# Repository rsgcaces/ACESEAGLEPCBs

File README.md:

# ACESEAGLEPCBs
Email Mr. D. if there is a design in the [ACES PCB Archive](http://darcy.rsgc.on.ca/ACES/PCBs/index.html) that you would like access to and he'll add it.

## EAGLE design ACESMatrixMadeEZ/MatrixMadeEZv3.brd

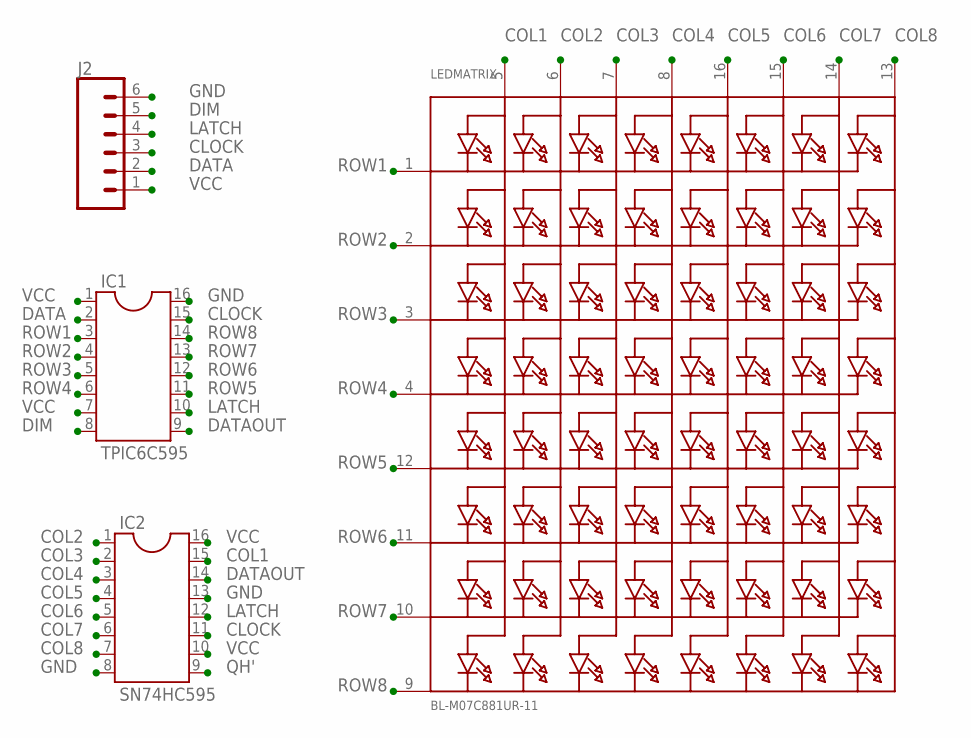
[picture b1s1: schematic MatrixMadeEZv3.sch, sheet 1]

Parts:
IC1: TPIC6C595; DIL16
IC2: SN74HC595; DIL16
J2: CONN_06LONGPADS; 1X06_LONGPADS
LEDMATRIX: BL-M07C881UR-11; SEGMENT_BL-M07C881UR

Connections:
CLOCK: IC1.15, IC2.11, J2.3
COL1: IC2.15, LEDMATRIX.5 (A1)
COL2: IC2.1, LEDMATRIX.6 (A2)
COL3: IC2.2, LEDMATRIX.7 (A3)
COL4: IC2.3, LEDMATRIX.8 (A4)
COL5: IC2.4, LEDMATRIX.16 (A5)
COL6: IC2.5, LEDMATRIX.15 (A6)
COL7: IC2.6, LEDMATRIX.14 (A7)
COL8: IC2.7, LEDMATRIX.13 (A8)
DATA: IC1.2, J2.2
DATAOUT: IC1.9, IC2.14
DIM: IC1.8, J2.5
GND: IC1.16, IC2.8, IC2.13, J2.6
LATCH: IC1.10, IC2.12, J2.4
QH': IC2.9
ROW1: IC1.3, LEDMATRIX.1 (K1)
ROW2: IC1.4, LEDMATRIX.2 (K2)
ROW3: IC1.5, LEDMATRIX.3 (K3)
ROW4: IC1.6, LEDMATRIX.4 (K4)
ROW5: IC1.11, LEDMATRIX.12 (K5)
ROW6: IC1.12, LEDMATRIX.11 (K6)
ROW7: IC1.13, LEDMATRIX.10 (K7)
ROW8: IC1.14, LEDMATRIX.9 (K8)
VCC: IC1.1, IC1.7, IC2.10, IC2.16, J2.1

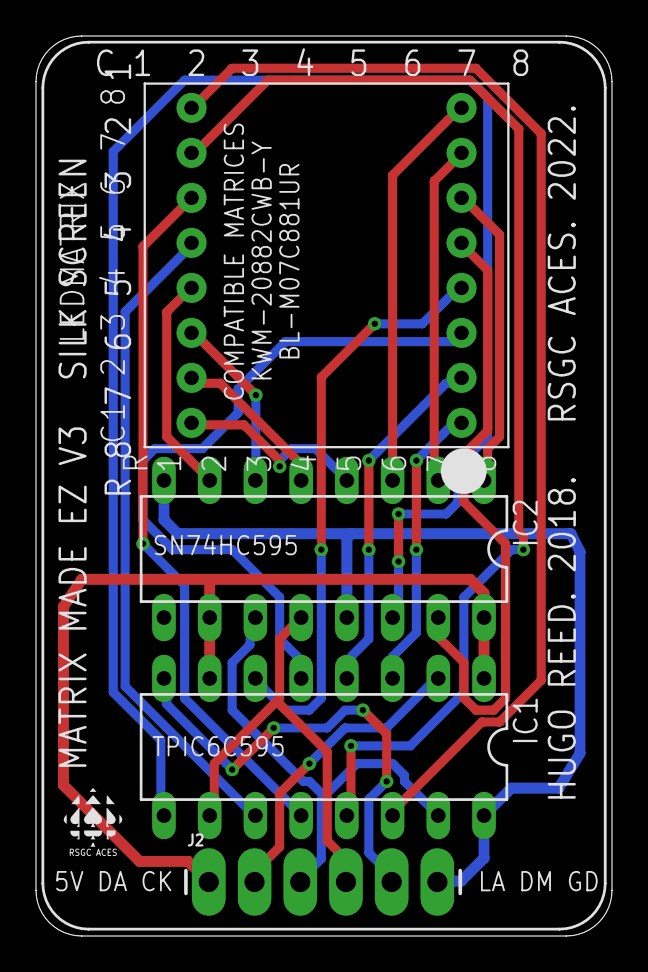
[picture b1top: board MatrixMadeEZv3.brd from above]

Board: 2 copper layers, 32.0 x 50.0 mm, 6 parts (0 on the bottom side), 23 nets.

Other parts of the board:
U$1: SMALL_TSILK_TEXT
U$6: SMALL_BSILK_TEXT

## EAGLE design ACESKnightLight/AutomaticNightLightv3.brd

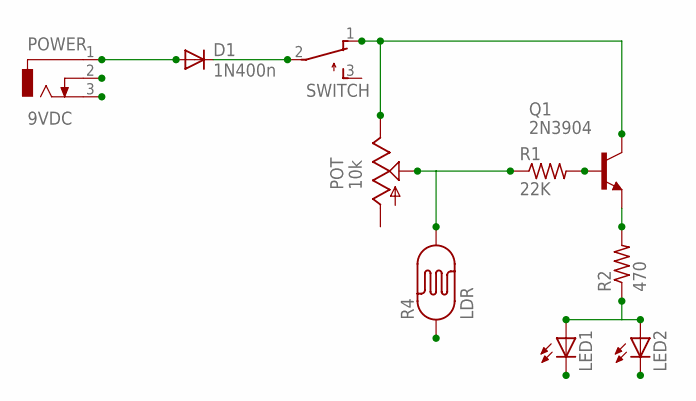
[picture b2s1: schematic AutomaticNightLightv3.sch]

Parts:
D1: 1N400n; DO41-10
LED1, LED2: LED5MM
POT: 10k; S64W
POWER: 9VDC; PJ-202AH
Q1: 2N3904; TO92-EBC-OVAL
R1: 22K; 0207/10
R2: 470; 0207/10
R4: LDR; PHOTOCELL
SWITCH: TL32PO; TL3XPO

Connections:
GND: LED1.K (C), LED2.K (C), POWER.2, POWER.3, R4.1
unnamed: D1.A, POWER.1
unnamed: D1.C, SWITCH.2
unnamed: Q1.B, R1.2
unnamed: Q1.E, R2.2
unnamed: POT.S, R1.1, R4.2
unnamed: POT.E, Q1.C, SWITCH.1 (O)
unnamed: LED1.A, LED2.A, R2.1

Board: 2 copper layers, 11 parts (0 on the bottom side), 8 nets, no tracks yet.

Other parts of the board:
U$1: MEDIUM_TSILK_TEXT

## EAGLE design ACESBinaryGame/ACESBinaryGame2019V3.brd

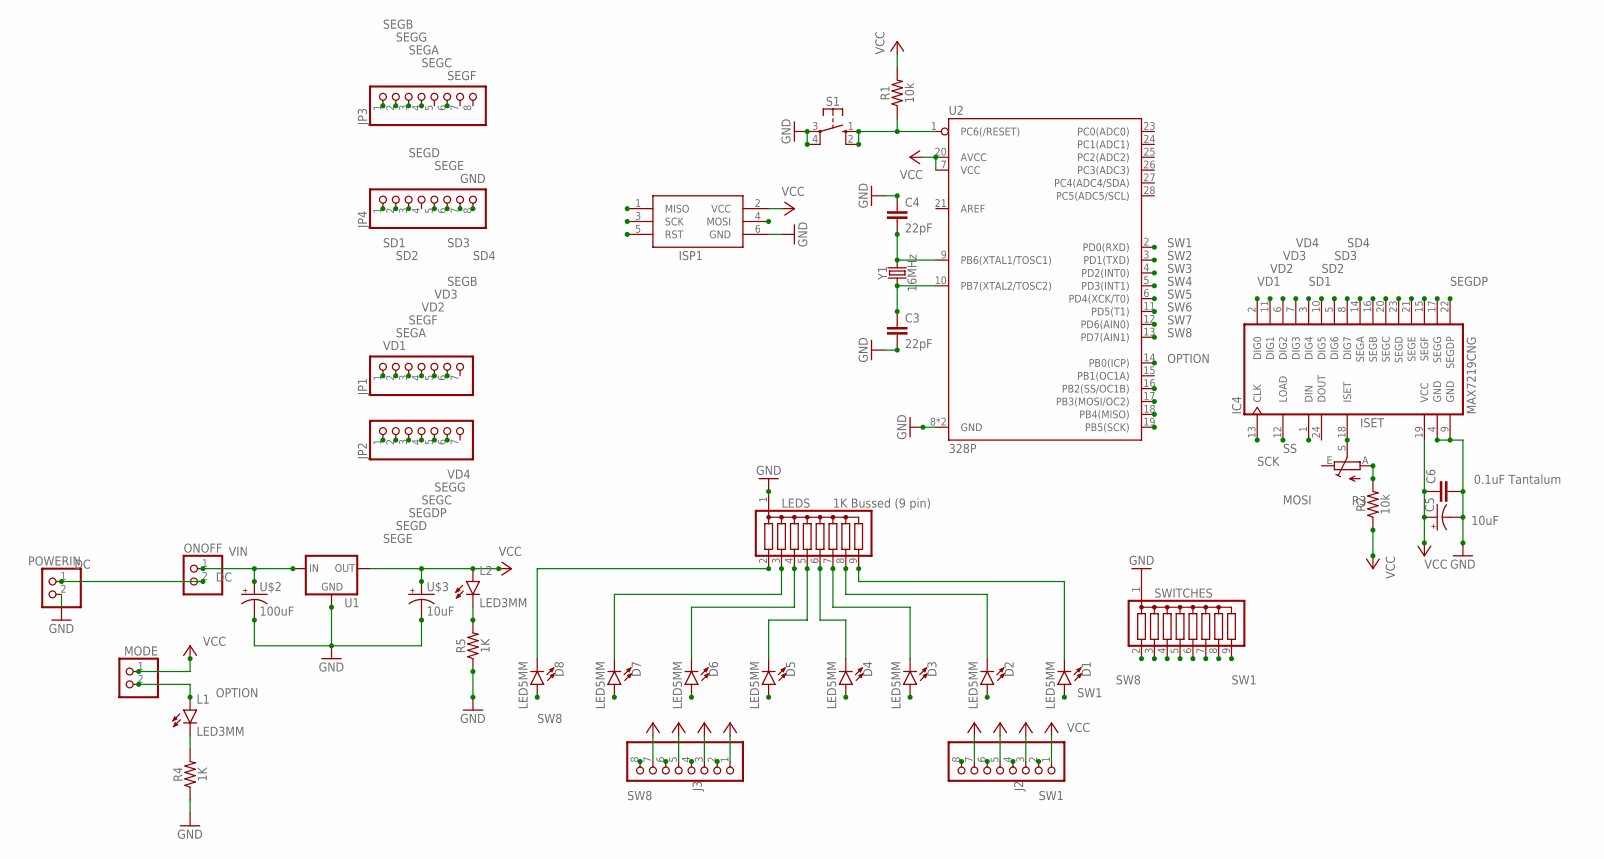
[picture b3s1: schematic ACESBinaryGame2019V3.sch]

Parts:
C3, C4: 22pF; CAP-PTH-2.54
C5: 10uF; CPOL-RADIAL-2.5MM-5MM
C6: 0.1uF Tantalum; CAP-PTH-2.54
D1, D2, D3, D4, D5, D6, D7, D8: LED5MM
IC4: MAX7219CNG; DIL24-3
ISP1: AVRISP-6; AVRISP
J2, J3: PINHD-1X8-3.5MM; 1X08-3.5MM
JP1, JP2: PINHD-1X7; 1X07
JP3, JP4: PINHD-1X8; 1X08
L1, L2: LED3MM
LEDS: 1K Bussed (9 pin); SIL9
MODE: PINHD-1X2; 1X02
ONOFF: PINHD-1X2; 1X02
POWERIN: PINHD-1X2; 1X02
R1, R2: 10k; AXIAL-0.3
R3: TRIM_EU-B25P; B25P
R4, R5: 1K; AXIAL-0.3
S1: MOMENTARY_BUTTONS; B3F-40XX
SWITCHES: G08R; SIL9
U1: LM78XX; 78XXL
U2: 328P; DIP28
U$2: 100uF; CPOL-RADIAL-2.5MM-5MM
U$3: 10uF; CPOL-RADIAL-2.5MM-5MM
Y1: 16MHz; HC49US

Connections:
DC: ONOFF.2, POWERIN.1
GND: C3.2, C4.1, C5.2 (-), C6.2, IC4.4 (GND), IC4.9 (GND), ISP1.6 (GND), JP4.7, LEDS.1, POWERIN.2, R4.P$1 (1), R5.P$1 (1), S1.3, S1.4 (P1), SWITCHES.1, U1.GND, U2.8 (GND), U2.22 (GND), U$2.2 (-), U$3.2 (-)
ISET: IC4.18 (ISET), R3.S
MISO: ISP1.1 (MISO), U2.18 (PB4(MISO))
MOSI: IC4.1 (DIN), ISP1.4 (MOSI), U2.17 (PB3(MOSI/OC2))
unnamed: L1.K (C), R4.P$2 (2)
unnamed: C3.1, U2.10 (PB7(XTAL2/TOSC2)), Y1.1
unnamed: C4.2, U2.9 (PB6(XTAL1/TOSC1)), Y1.2
unnamed: R2.P$2 (2), R3.A
unnamed: L2.K (C), R5.P$2 (2)
unnamed: D1.K (C), LEDS.9
unnamed: D2.K (C), LEDS.8
unnamed: D3.K (C), LEDS.7
unnamed: D4.K (C), LEDS.6
unnamed: D5.K (C), LEDS.5
unnamed: D6.K (C), LEDS.4
unnamed: D7.K (C), LEDS.3
unnamed: D8.K (C), LEDS.2
OPTION: L1.A, MODE.2, U2.14 (PB0(ICP))
RST: ISP1.5 (RST), R1.P$1 (1), S1.1 (S), S1.2 (S1), U2.1 (PC6(/RESET))
SCK: IC4.13 (CLK), ISP1.3 (SCK), U2.19 (PB5(SCK))
SD1: IC4.3 (DIG4), JP4.1
SD2: IC4.10 (DIG5), JP4.2
SD3: IC4.5 (DIG6), JP4.6
SD4: IC4.8 (DIG7), JP4.8
SEGA: IC4.14 (SEGA), JP1.2, JP3.3
SEGB: IC4.16 (SEGB), JP1.6, JP3.1
SEGC: IC4.20 (SEGC), JP2.4, JP3.4
SEGD: IC4.23 (SEGD), JP2.2, JP4.3
SEGDP: IC4.22 (SEGDP), JP2.3
SEGE: IC4.21 (SEGE), JP2.1, JP4.5
SEGF: IC4.15 (SEGF), JP1.3, JP3.6
SEGG: IC4.17 (SEGG), JP2.5, JP3.2
SS: IC4.12 (LOAD), U2.16 (PB2(SS/OC1B))
SW1: D1.A, J2.2, SWITCHES.9, U2.2 (PD0(RXD))
SW2: D2.A, J2.4, SWITCHES.8, U2.3 (PD1(TXD))
SW3: D3.A, J2.6, SWITCHES.7, U2.4 (PD2(INT0))
SW4: D4.A, J2.8, SWITCHES.6, U2.5 (PD3(INT1))
SW5: D5.A, J3.2, SWITCHES.5, U2.6 (PD4(XCK/T0))
SW6: D6.A, J3.4, SWITCHES.4, U2.11 (PD5(T1))
SW7: D7.A, J3.6, SWITCHES.3, U2.12 (PD6(AIN0))
SW8: D8.A, J3.8, SWITCHES.2, U2.13 (PD7(AIN1))
VCC: C5.1 (+), C6.1, IC4.19 (VCC), ISP1.2 (VCC), J2.1, J2.3, J2.5, J2.7, J3.1, J3.3, J3.5, J3.7, L2.A, MODE.1, R1.P$2 (2), R2.P$1 (1), U1.OUT, U2.7 (VCC), U2.20 (AVCC), U$3.1 (+)
VD1: IC4.2 (DIG0), JP1.1
VD2: IC4.11 (DIG1), JP1.4
VD3: IC4.6 (DIG2), JP1.5
VD4: IC4.7 (DIG3), JP2.6
VIN: ONOFF.1, U1.IN, U$2.1 (+)

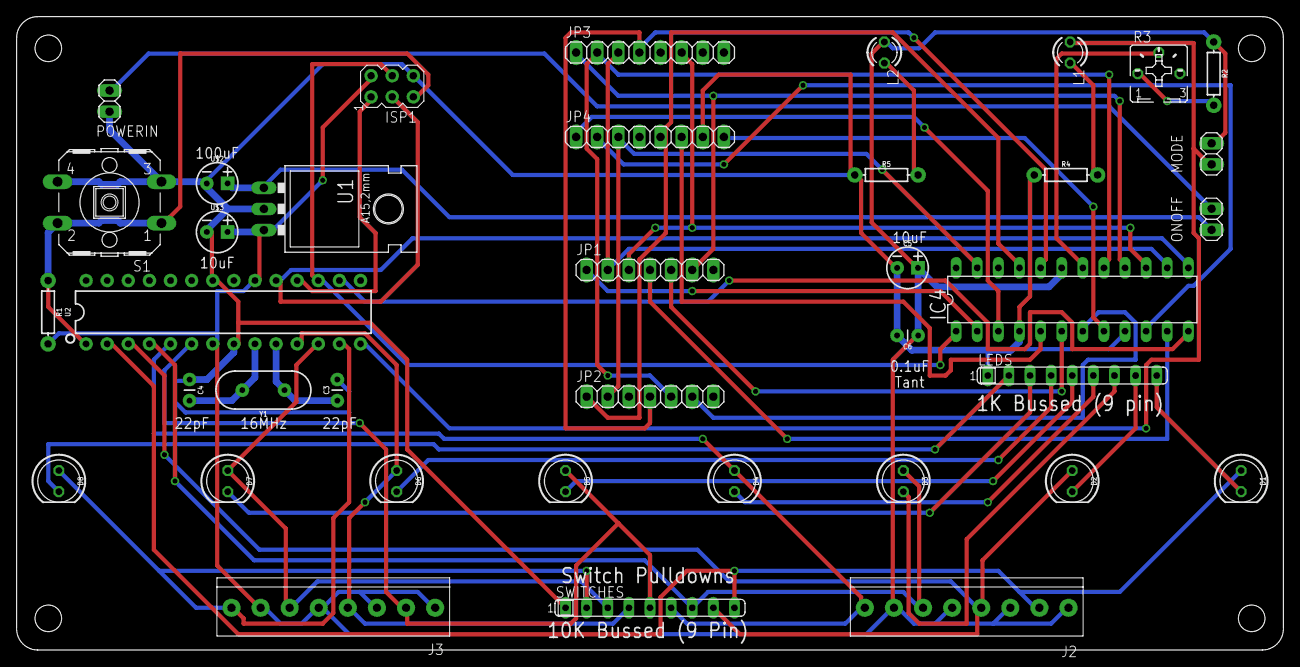
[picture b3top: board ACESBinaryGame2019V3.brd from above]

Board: 2 copper layers, 152.4 x 76.2 mm, 39 parts (0 on the bottom side), 48 nets.

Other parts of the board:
U$1: ACES_LOGO_MEDIUM

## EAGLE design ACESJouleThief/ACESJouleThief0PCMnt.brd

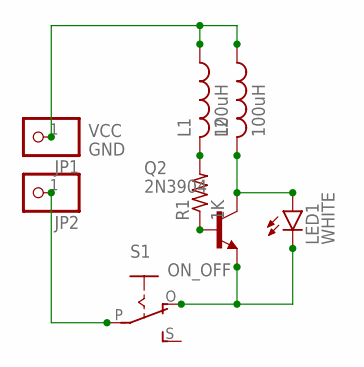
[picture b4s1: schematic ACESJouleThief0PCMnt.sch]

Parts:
JP1, JP2: PINHD-1X1; 1X01
L1, L2: 100uH; 0207/10
LED1: WHITE; LED_5MM
Q2: 2N3904; TO92-EBC
R1: 1K; 0207/10
S1: ON_OFF; EG1218

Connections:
GND: JP2.1, S1.P
unnamed: Q2.B, R1.1
unnamed: LED1.K (C), Q2.E, S1.O
unnamed: L2.2, LED1.A, Q2.C
unnamed: L1.2, R1.2
VCC: JP1.1, L1.1, L2.1

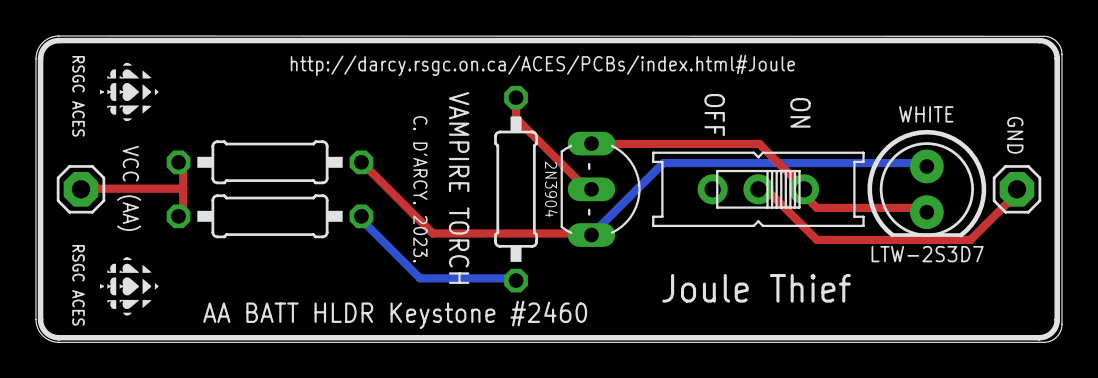
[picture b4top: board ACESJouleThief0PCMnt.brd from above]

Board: 2 copper layers, 57.0 x 17.0 mm, 11 parts (0 on the bottom side), 6 nets.

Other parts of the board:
U$1, U$2: SMALL_TSILK
U$3: MEDIUM_BSILK_TEXT

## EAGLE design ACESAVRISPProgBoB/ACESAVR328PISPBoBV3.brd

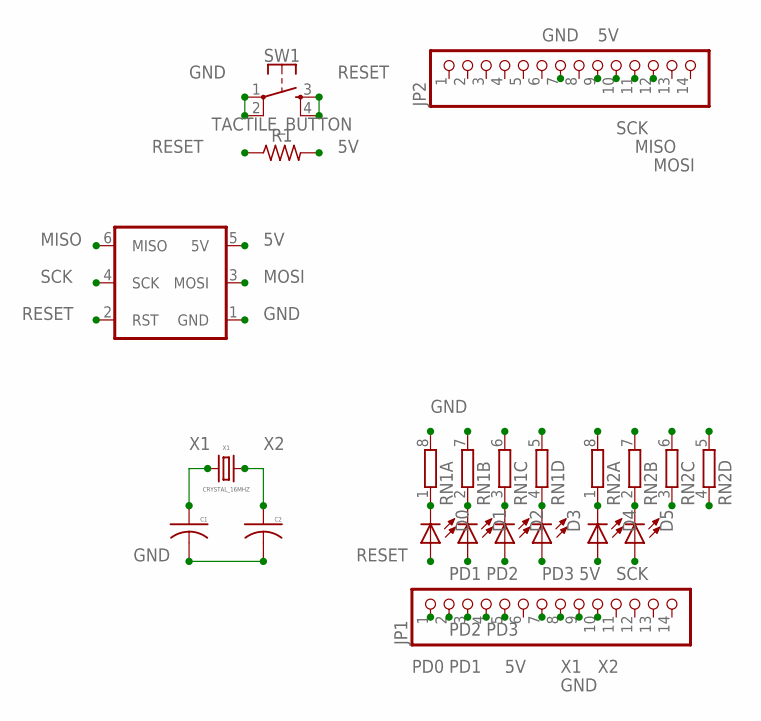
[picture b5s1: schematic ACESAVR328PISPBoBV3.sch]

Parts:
C1, C2: C-USC0603K; C0603K
D0, D1, D2, D3: BLUE; CHIP-LED0603
D4: RED; CHIP-LED0603
D5: GREEN; CHIP-LED0603
H1: ISP_HEADER; ICSP
JP1, JP2: PINHD-1X14; 1X14
R1: R-US_R0603; R0603
RN1, RN2: 4R-N0603-ARC; 0603-ARC
SW1: TACTILE_BUTTON; TACTILE_BUTTON_SMD_5.2MM
X1: CRYSTAL_16MHZ; HC49US

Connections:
5V: D4.A, H1.5 (5V), JP1.7, JP2.9, R1.2
GND: C1.2, C2.2, H1.1 (GND), JP1.8, JP2.7, RN1.5 (2), RN1.6 (2), RN1.7 (2), RN1.8 (2), RN2.5 (2), RN2.6 (2), RN2.7 (2), RN2.8 (2), SW1.1, SW1.2
MISO: H1.6 (MISO), JP2.11
MOSI: H1.3 (MOSI), JP2.12
unnamed: D0.C, RN1.1
unnamed: D1.C, RN1.2 (1)
unnamed: D2.C, RN1.3 (1)
unnamed: D3.C, RN1.4 (1)
unnamed: D4.C, RN2.1
unnamed: D5.C, RN2.2 (1)
PD0: D0.A, JP1.2
PD1: D1.A, JP1.3
PD2: D2.A, JP1.4
PD3: D3.A, JP1.5
RESET: H1.2 (RST), JP1.1, R1.1, SW1.3, SW1.4
SCK: D5.A, H1.4 (SCK), JP2.10
X1: C1.1, JP1.9, X1.1
X2: C2.1, JP1.10, X1.2

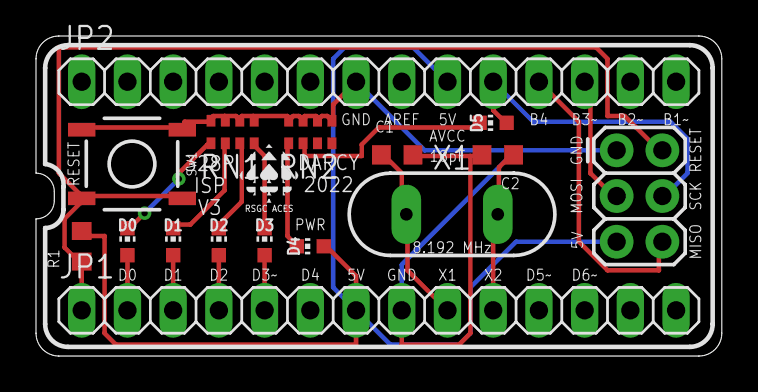
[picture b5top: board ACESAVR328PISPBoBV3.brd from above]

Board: 2 copper layers, 38.1 x 17.8 mm, 17 parts (0 on the bottom side), 18 nets.

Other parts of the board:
U$1: SMALL_TSILK_TEXT

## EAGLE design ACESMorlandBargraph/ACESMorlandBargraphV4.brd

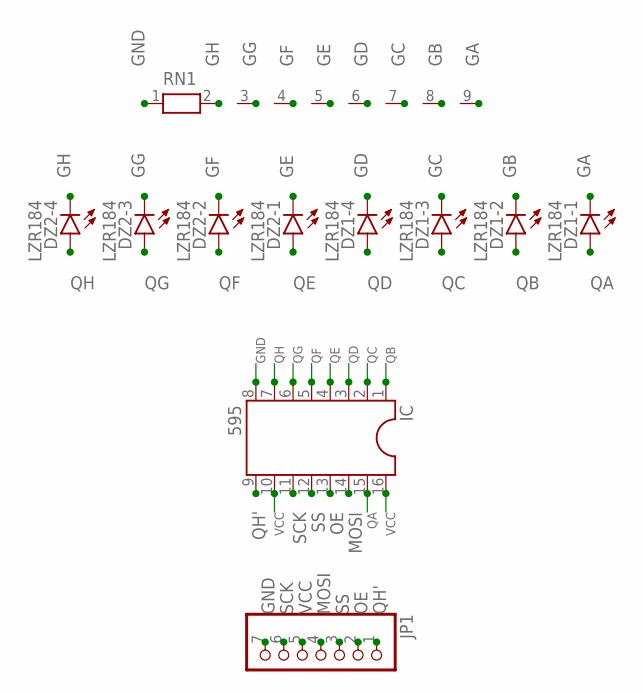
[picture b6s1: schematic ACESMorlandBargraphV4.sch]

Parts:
DZ1, DZ2: LZR184
IC: 595; DIL16
JP1: PINHD-1X7/90; 1X07/90
RN1: RN08; RN-9

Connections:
GA: DZ1.K1 (C), RN1.9
GB: DZ1.K2 (C), RN1.8
GC: DZ1.K3 (C), RN1.7
GD: DZ1.K4 (C), RN1.6
GE: DZ2.K1 (C), RN1.5
GF: DZ2.K2 (C), RN1.4
GG: DZ2.K3 (C), RN1.3
GH: DZ2.K4 (C), RN1.2
GND: IC.8, JP1.7, RN1.1
MOSI: IC.14, JP1.4
OE: IC.13, JP1.2
QA: DZ1.A1 (A), IC.15
QB: DZ1.A2 (A), IC.1
QC: DZ1.A3 (A), IC.2
QD: DZ1.A4 (A), IC.3
QE: DZ2.A1 (A), IC.4
QF: DZ2.A2 (A), IC.5
QG: DZ2.A3 (A), IC.6
QH: DZ2.A4 (A), IC.7
QH': IC.9, JP1.1
SCK: IC.11, JP1.6
SS: IC.12, JP1.3
VCC: IC.10, IC.16, JP1.5

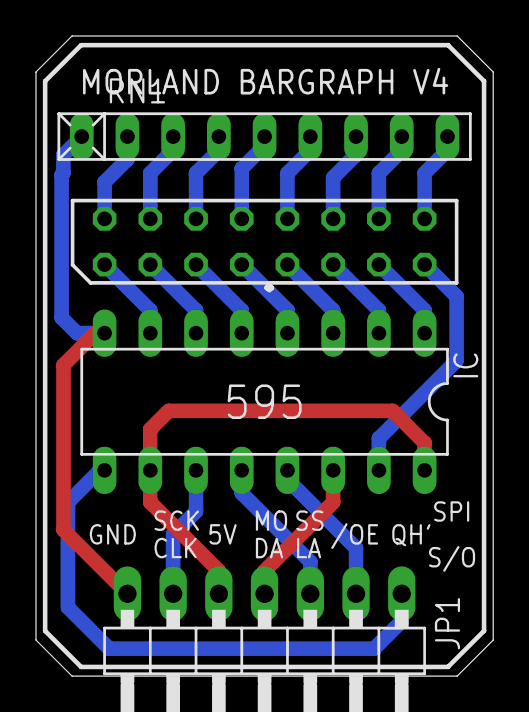
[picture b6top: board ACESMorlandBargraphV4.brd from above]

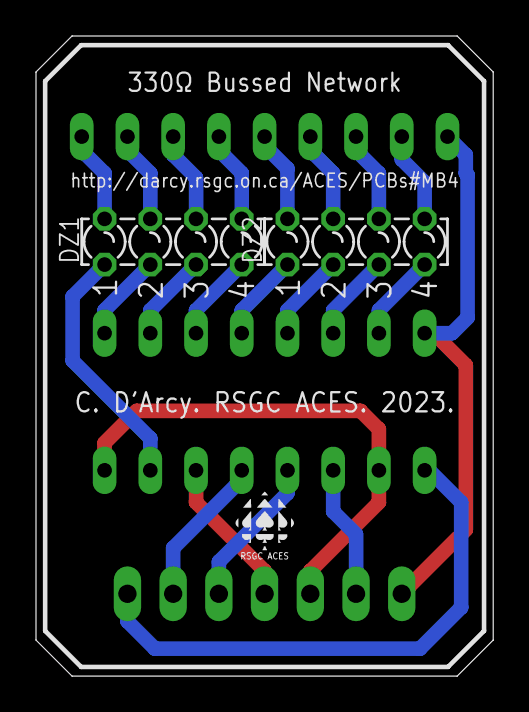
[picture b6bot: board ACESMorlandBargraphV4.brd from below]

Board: 2 copper layers, 25.4 x 35.6 mm, 6 parts (2 on the bottom side), 23 nets.

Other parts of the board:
U$1: SMALL_BSILK_TEXT

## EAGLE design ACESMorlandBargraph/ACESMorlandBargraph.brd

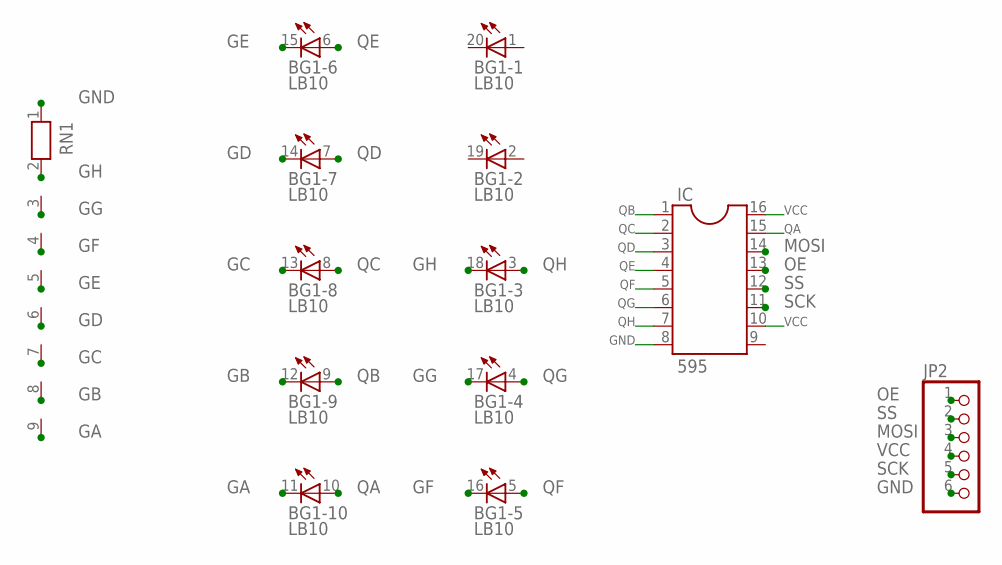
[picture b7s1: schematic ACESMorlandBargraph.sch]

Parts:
BG1: LB10
IC: 595; DIL16
JP2: PINHD-1X6/90; 1X06/90
RN1: RN08; RN-9

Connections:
GA: BG1.11 (C), RN1.9
GB: BG1.12 (C), RN1.8
GC: BG1.13 (C), RN1.7
GD: BG1.14 (C), RN1.6
GE: BG1.15 (C), RN1.5
GF: BG1.16 (C), RN1.4
GG: BG1.17 (C), RN1.3
GH: BG1.18 (C), RN1.2
GND: IC.8, JP2.6, RN1.1
MOSI: IC.14, JP2.3
OE: IC.13, JP2.1
QA: BG1.10 (A), IC.15
QB: BG1.9 (A), IC.1
QC: BG1.8 (A), IC.2
QD: BG1.7 (A), IC.3
QE: BG1.6 (A), IC.4
QF: BG1.5 (A), IC.5
QG: BG1.4 (A), IC.6
QH: BG1.3 (A), IC.7
SCK: IC.11, JP2.5
SS: IC.12, JP2.2
VCC: IC.10, IC.16, JP2.4

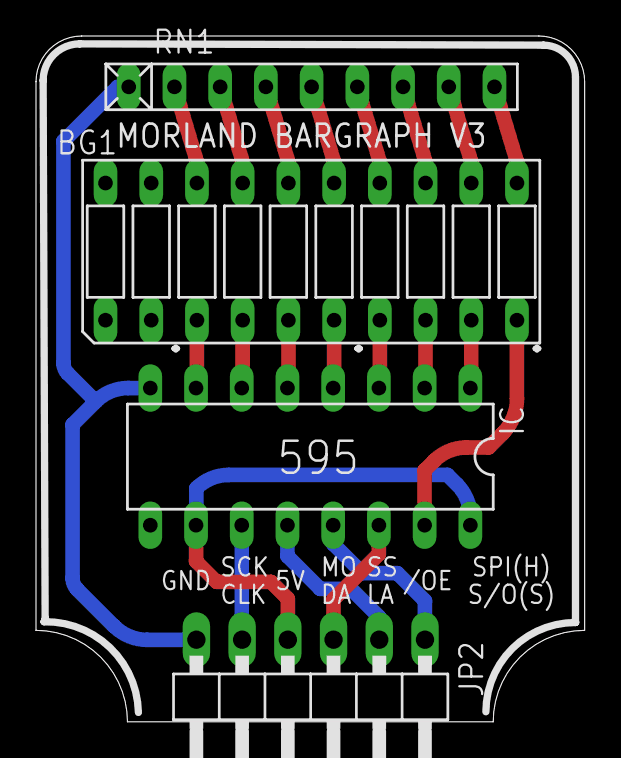
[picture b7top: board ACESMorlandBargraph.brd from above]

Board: 2 copper layers, 30.5 x 38.1 mm, 4 parts (0 on the bottom side), 22 nets.

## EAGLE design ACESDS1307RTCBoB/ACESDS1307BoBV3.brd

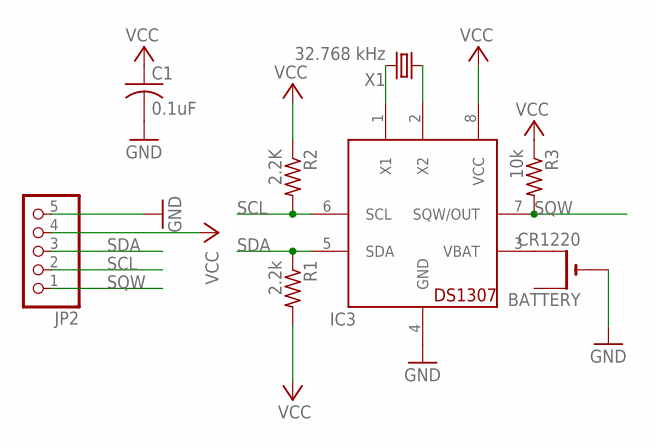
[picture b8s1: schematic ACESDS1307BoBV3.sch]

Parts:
BATTERY: CR1220; CR1220-THM
C1: 0.1uF; C025-025X050
IC3: DS1307; DIL08
JP2: PINHD-1X5; 1X05
R1: 2.2k; 0207/10
R2: 2.2K; 0207/10
R3: 10k; 0207/10
X1: 32.768 kHz; TC38H

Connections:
GND: BATTERY.-, C1.2, IC3.4 (GND), JP2.5
unnamed: IC3.1 (X1), X1.2
unnamed: IC3.2 (X2), X1.1
unnamed: BATTERY.+2 (+1), IC3.3 (VBAT)
SCL: IC3.6 (SCL), JP2.2, R2.2
SDA: IC3.5 (SDA), JP2.3, R1.1
SQW: IC3.7 (SQW/OUT), JP2.1, R3.2
VCC: C1.1, IC3.8 (VCC), JP2.4, R1.2, R2.1, R3.1

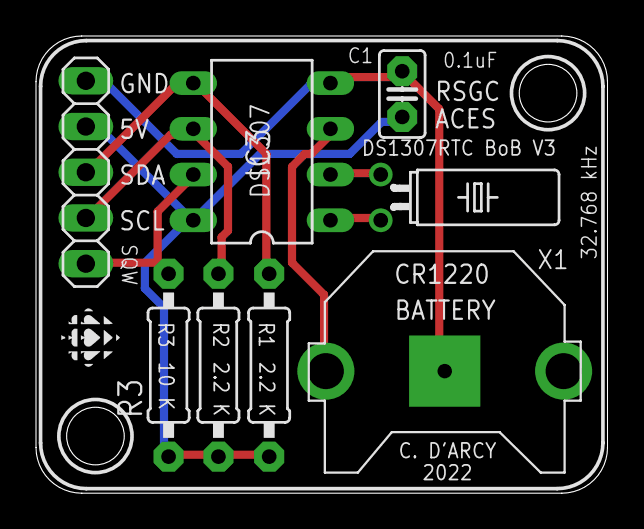
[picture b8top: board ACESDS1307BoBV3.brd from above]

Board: 2 copper layers, 31.8 x 25.4 mm, 10 parts (0 on the bottom side), 8 nets.

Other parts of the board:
U$1: MEDIUM_BSILK_TEXT
U$2: SMALL_TSILK

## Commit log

2023-01-28 ACES Adaptations of Adafruit's Perma-Protos Boards
2023-01-28 ACES adaptation of Adafruit's DS1307 Breakout Baord
2023-01-28 ACES
2023-01-28 ACES' Adaptations of Adafruit's DS1307RTC Breakout Board
2023-01-31 Morland Bargraph Versions
2023-01-31 ACES AVR ISP Breakout Board V3
2023-01-31 ACES' Joule Thief
    Designed for Keystone #2460 AA Battery Holder.
2023-01-31 ACES' Binary Game V3
2023-01-31 ACES' Knight Light
2023-01-31 ACES Matrix Made EZ V3
    Based on H. Reed's initial design.
2023-03-23 Developed for ICS3U-E ACES
    A Fusion 360 parametrically-driven PCB case design for ACES to house their projects
2023-03-24 Removed

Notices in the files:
parts and their libraries:
SparkFun-IC-Microcontroller: Licensing: Creative Commons ShareAlike 4.0 International - https://creativecommons.org/licenses/by-sa/4.0
